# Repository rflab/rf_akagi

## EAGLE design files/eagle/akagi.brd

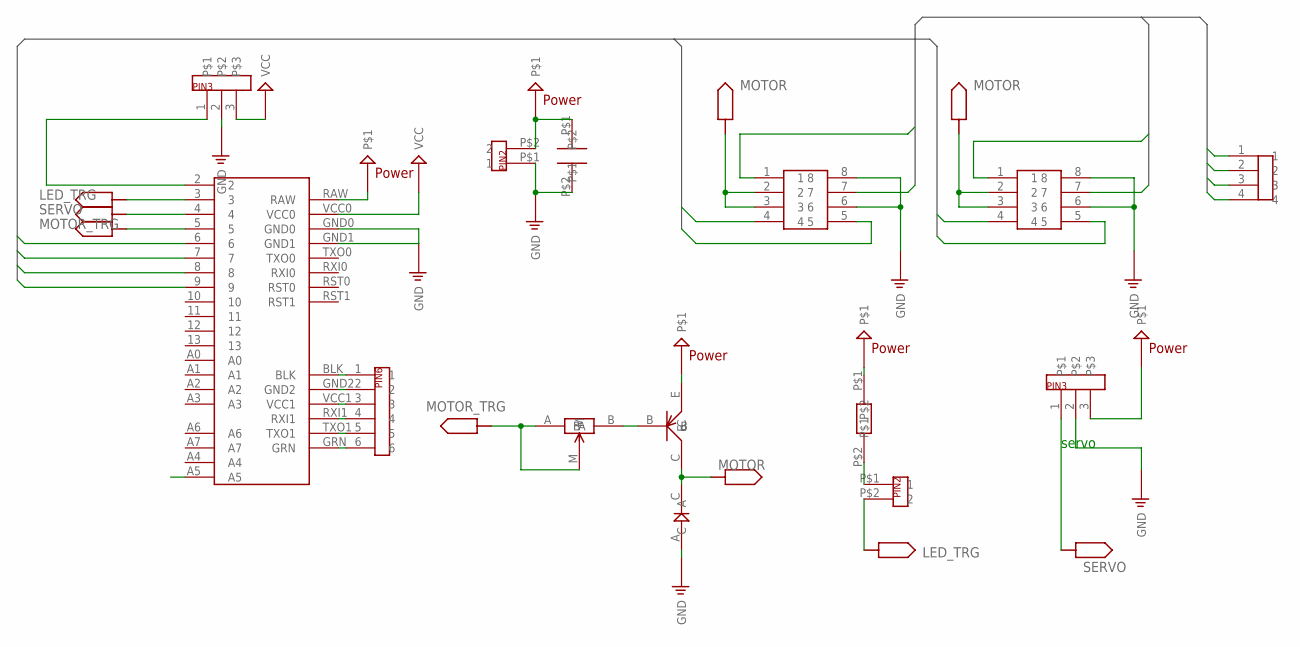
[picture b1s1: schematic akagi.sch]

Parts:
U$1: ARDUINO_PRO_MINI
U$2, U$9: PIN3
U$4, U$37: PIN2
U$5: PIN_4_1
U$7: TRANSISTOR_PNP; TRANSISTOR
U$8: CAPACITOR
U$14: REGISTER
U$15: RESISTOR_VALIABLE
U$17: DIORDE
U$21, U$26: DIP8
U$34: PIN6

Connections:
B$0: U$5.1, U$21.1
B$1: U$5.2, U$21.7
B$2: U$5.3, U$26.1
B$3: U$5.4, U$26.7
GND: U$1.GND0, U$1.GND1, U$2.2, U$4.P$1 (1), U$8.P$2, U$9.2, U$17.A, U$21.6, U$21.8, U$26.6, U$26.8
LED_TRG: U$1.3, U$37.P$2 (2)
MOTER_SIGNAL0: U$1.6, U$21.4
MOTER_SIGNAL1: U$1.7, U$21.5
MOTER_SIGNAL2: U$1.8, U$26.4
MOTER_SIGNAL3: U$1.9, U$26.5
MOTOR: U$7.C, U$17.C, U$21.2, U$21.3, U$26.2, U$26.3
MOTOR_TRG: U$1.5, U$15.A, U$15.M
unnamed: U$1.2, U$9.1
unnamed: U$14.P$2, U$37.P$1 (1)
unnamed: U$1.GRN, U$34.6
unnamed: U$1.TXO1, U$34.5
unnamed: U$1.RXI1, U$34.4
unnamed: U$1.VCC1, U$34.3
unnamed: U$1.GND2, U$34.2
unnamed: U$1.BLK, U$34.1
unnamed: U$7.B, U$15.B
P$1: U$1.RAW, U$2.3, U$4.P$2 (2), U$7.E, U$8.P$1, U$14.P$1
SERVO: U$1.4, U$2.1
VCC: U$1.VCC0, U$9.3

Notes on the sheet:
servo

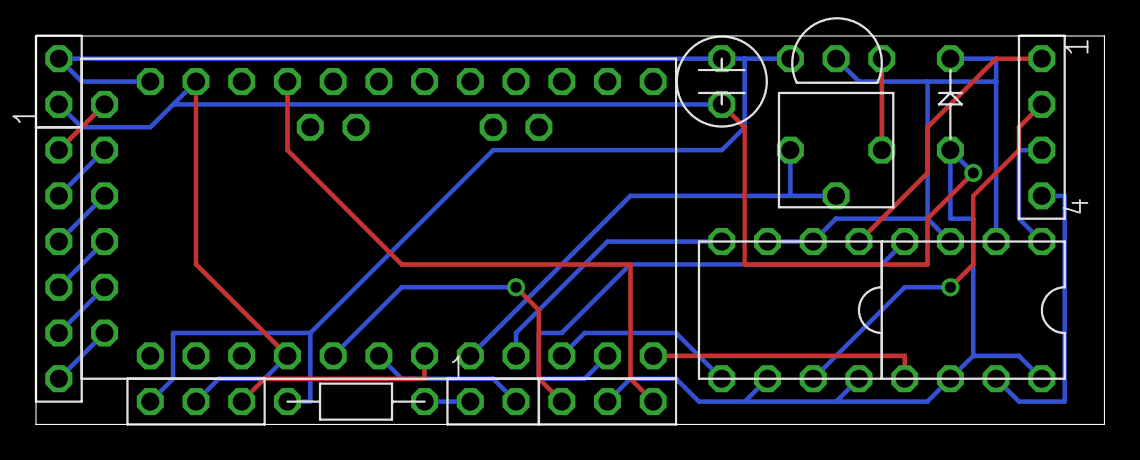
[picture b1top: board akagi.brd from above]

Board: 2 copper layers, 59.4 x 21.6 mm, 14 parts (0 on the bottom side), 24 nets.

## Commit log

2014-08-16 :lollipop: Added .gitattributes & .gitignore files
2014-08-16 add files
